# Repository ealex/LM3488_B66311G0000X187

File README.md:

# LM3488_B66311G0000X187
LM3488 based flyback using B66311G0000X187 core and B66206B1110T001 coil former

The coil former will have most of it's pins used, one pair for the primary and 3 for the secondaries

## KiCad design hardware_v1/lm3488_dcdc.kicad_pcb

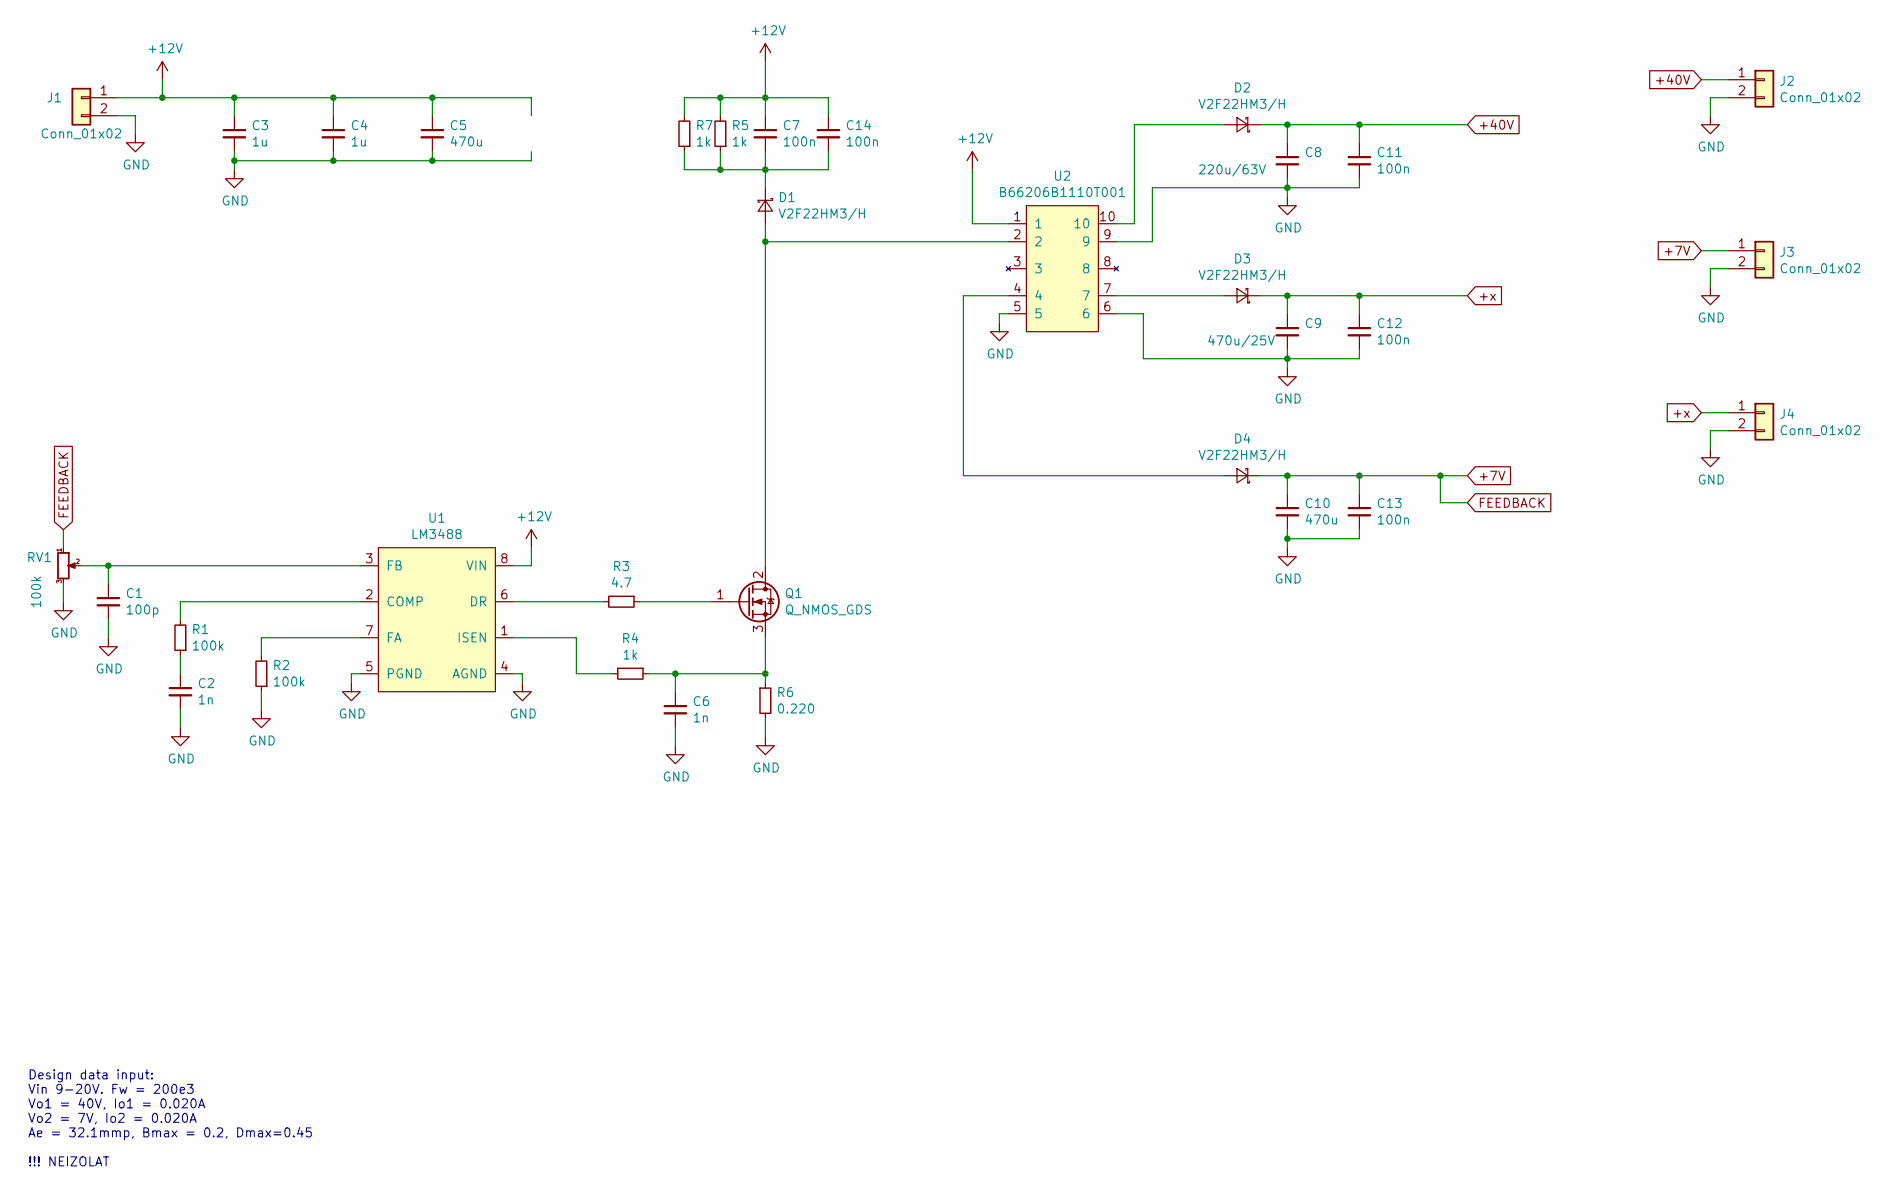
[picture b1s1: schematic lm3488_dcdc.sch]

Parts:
C1: 100p; C_1206_3216Metric
C2, C6: 1n; C_1206_3216Metric
C3, C4: 1u; C_0805_2012Metric
C5, C10: 470u; CP_Radial_D10.0mm_P5.00mm
C7, C11, C12, C13, C14: 100n; C_1206_3216Metric
C8: 220u/63V; CP_Radial_D10.0mm_P5.00mm
C9: 470u/25V; CP_Radial_D10.0mm_P5.00mm
D1, D2, D3, D4: V2F22HM3/H; D_SMF
J1, J2, J3, J4: Conn_01x02; eylet_connector
Q1: Q_NMOS_GDS; TO-220-3_Vertical
R1, R2: 100k; R_1206_3216Metric
R3: 4.7; R_1206_3216Metric
R4, R5, R7: 1k; R_1206_3216Metric
R6: 0.220; R_1206_3216Metric
RV1: 100k; pot_multiturn
U1: LM3488
U2: B66206B1110T001

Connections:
+7V: C10.1, C13.1, D4.1 (K), J3.1, RV1.1
+12V: C3.1, C4.1, C5.1, C7.1, C14.1, J1.1, R5.2, R7.2, U1.8 (VIN), U2.1
+40V: C8.1, C11.1, D2.1 (K), J2.1
+x: C9.1, C12.1, D3.1 (K), J4.1
GND: C1.2, C2.2, C3.2, C4.2, C5.2, C6.2, C8.2, C9.2, C10.2, C11.2, C12.2, C13.2, J1.2, J2.2, J3.2, J4.2, R2.1, R6.2, RV1.3, U1.4 (AGND), U1.5 (PGND), U2.5, U2.6, U2.9
unnamed: C1.1, RV1.2, U1.3 (FB)
unnamed: C2.1, R1.1
unnamed: C6.1, Q1.3 (S), R4.1, R6.1
unnamed: C7.2, C14.2, D1.1 (K), R5.1, R7.1
unnamed: D1.2 (A), Q1.2 (D), U2.2
unnamed: D2.2 (A), U2.10
unnamed: D3.2 (A), U2.7
unnamed: D4.2 (A), U2.4
unnamed: Q1.1 (G), R3.1
unnamed: R1.2, U1.2 (COMP)
unnamed: R2.2, U1.7 (FA)
unnamed: R3.2, U1.6 (DR)
unnamed: R4.2, U1.1 (ISEN)

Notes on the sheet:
Design data input: Vin 9-20V. Fw = 200e3 Vo1 = 40V, Io1 = 0.020A Vo2 = 7V, Io2 = 0.020A Ae = 32.1mmp, Bmax = 0.2, Dmax=0.45 !!! NEIZOLAT

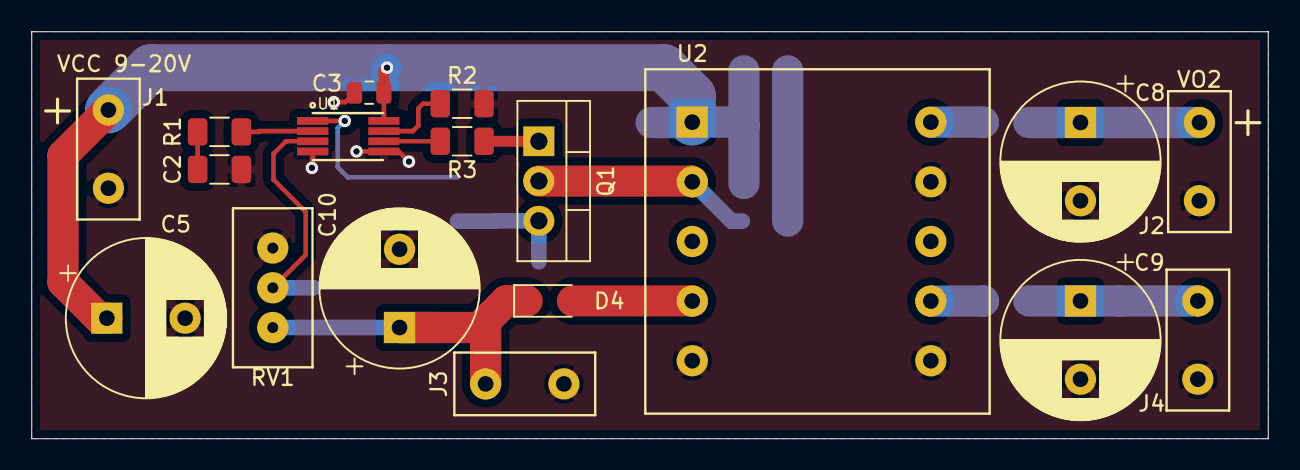
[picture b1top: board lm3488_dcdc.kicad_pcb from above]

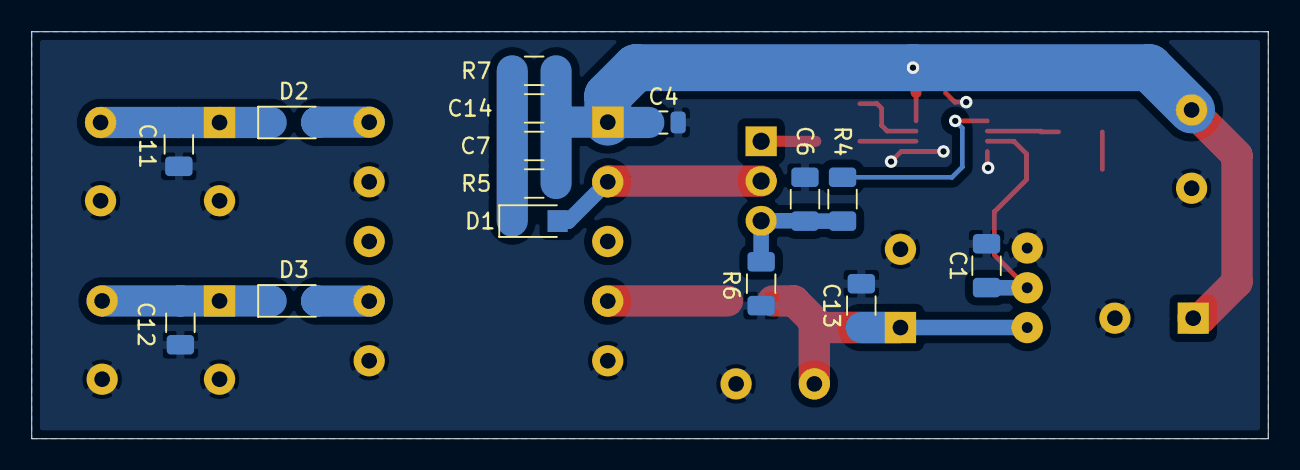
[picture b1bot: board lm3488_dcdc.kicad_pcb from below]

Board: 2 copper layers, 79.0 x 26.0 mm, 33 parts (15 on the bottom side), 18 nets.

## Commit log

2021-01-28 add smps controller and core documentation
2021-01-28 add schematic
2021-02-02 final touch ups and production data
